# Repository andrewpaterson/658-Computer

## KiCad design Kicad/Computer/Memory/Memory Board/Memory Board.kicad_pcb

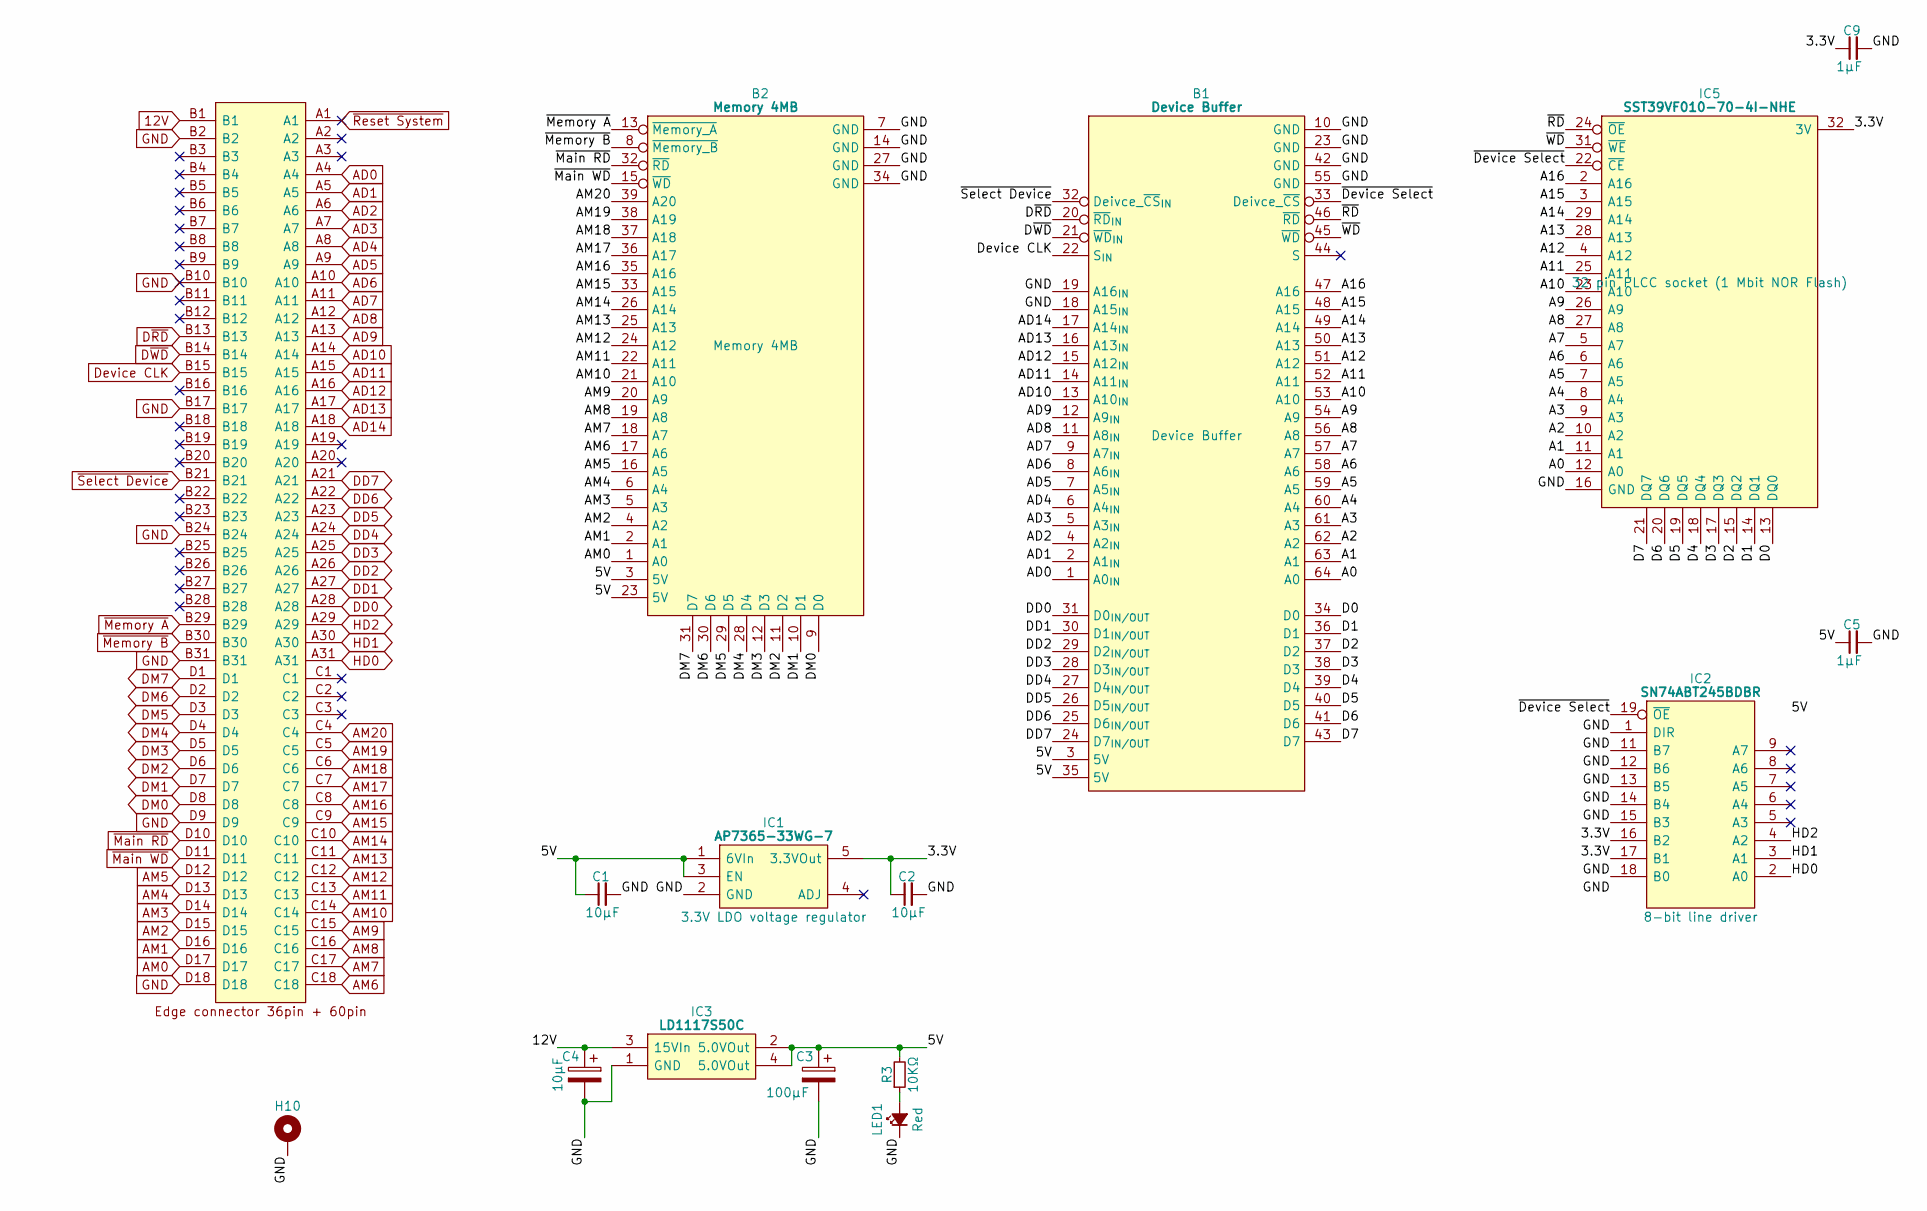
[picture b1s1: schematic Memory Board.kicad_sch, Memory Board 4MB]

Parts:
B1: Device Buffer; HCP65_Device_Buffer
B2: Memory 4MB; HCP65_Memory_4MB
C1, C2: 10µF; C_0805
C3: 100μF; CP_Radial_D4.0mm_P2.00mm
C4: 10μF; CP_Radial_D4.0mm_P2.00mm
C5, C9: 1µF; C_0805
H10: MountingHole_Pad; HCP65_MountingHole_M3_
IC1: AP7365-33WG-7; SOT95P285X130-5N; Manufacturer_Part_Number AP7365-33WG-7; Mouser Part Number 621-AP7365-33WG-7
IC2: SN74ABT245BDBR; SOP65P780X200-20N; Manufacturer_Part_Number SN74ABT245BDBR; Mouser Part Number 595-SN74ABT245BDBR
IC3: LD1117S50C; LD1117S33C; Manufacturer_Part_Number LD1117S50C
IC5: SST39VF010-70-4I-NHE; 5408803224008; Manufacturer_Part_Number SST39VF010-70-4I-NHE
J1: 395-098-520-350; 98pin Edge Connector; Manufacturer_Part_Number 395-098-520-350; Mouser Part Number 587-395-098-520-350
LED1: Red; LED_D5.0mm
R3: 10KΩ; R_0805

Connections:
12V: C4.1, IC3.3 (15VIn), J1.B1
/3.3V: C2.1, C9.1, IC1.5 (3.3VOut), IC2.16 (B2), IC2.17 (B1), IC5.32 (3V)
/5V: B1.3 (5V), B1.35 (5V), B2.3 (5V), B2.23 (5V), C1.1, C3.1, C5.1, IC1.1 (6VIn), IC1.3 (EN), IC2.20 (5V), IC3.2 (5.0VOut), IC3.4 (5.0VOut), R3.2
/A0: B1.64 (A0), IC5.12 (A0)
/A1: B1.63 (A1), IC5.11 (A1)
/A2: B1.62 (A2), IC5.10 (A2)
/A3: B1.61 (A3), IC5.9 (A3)
/A4: B1.60 (A4), IC5.8 (A4)
/A5: B1.59 (A5), IC5.7 (A5)
/A6: B1.58 (A6), IC5.6 (A6)
/A7: B1.57 (A7), IC5.5 (A7)
/A8: B1.56 (A8), IC5.27 (A8)
/A9: B1.54 (A9), IC5.26 (A9)
/A10: B1.53 (A10), IC5.23 (A10)
/A11: B1.52 (A11), IC5.25 (A11)
/A12: B1.51 (A12), IC5.4 (A12)
/A13: B1.50 (A13), IC5.28 (A13)
/A14: B1.49 (A14), IC5.29 (A14)
/A15: B1.48 (A15), IC5.3 (A15)
/A16: B1.47 (A16), IC5.2 (A16)
/D0: B1.34 (D0), IC5.13 (DQ0)
/D1: B1.36 (D1), IC5.14 (DQ1)
/D2: B1.37 (D2), IC5.15 (DQ2)
/D3: B1.38 (D3), IC5.17 (DQ3)
/D4: B1.39 (D4), IC5.18 (DQ4)
/D5: B1.40 (D5), IC5.19 (DQ5)
/D6: B1.41 (D6), IC5.20 (DQ6)
/D7: B1.43 (D7), IC5.21 (DQ7)
/~Device Select: B1.33 (Deivce_~CS), IC2.19 (~OE), IC5.22 (~CE)
/~RD: B1.46 (~RD), IC5.24 (~OE)
/~WD: B1.45 (~WD), IC5.31 (~WE)
AD0: B1.1 (A0_{IN}), J1.A4
AD1: B1.2 (A1_{IN}), J1.A5
AD2: B1.4 (A2_{IN}), J1.A6
AD3: B1.5 (A3_{IN}), J1.A7
AD4: B1.6 (A4_{IN}), J1.A8
AD5: B1.7 (A5_{IN}), J1.A9
AD6: B1.8 (A6_{IN}), J1.A10
AD7: B1.9 (A7_{IN}), J1.A11
AD8: B1.11 (A8_{IN}), J1.A12
AD9: B1.12 (A9_{IN}), J1.A13
AD10: B1.13 (A10_{IN}), J1.A14
AD11: B1.14 (A11_{IN}), J1.A15
AD12: B1.15 (A12_{IN}), J1.A16
AD13: B1.16 (A13_{IN}), J1.A17
AD14: B1.17 (A14_{IN}), J1.A18
AM0: B2.1 (A0), J1.D17
AM1: B2.2 (A1), J1.D16
AM2: B2.4 (A2), J1.D15
AM3: B2.5 (A3), J1.D14
AM4: B2.6 (A4), J1.D13
AM5: B2.16 (A5), J1.D12
AM6: B2.17 (A6), J1.C18
AM7: B2.18 (A7), J1.C17
AM8: B2.19 (A8), J1.C16
AM9: B2.20 (A9), J1.C15
AM10: B2.21 (A10), J1.C14
AM11: B2.22 (A11), J1.C13
AM12: B2.24 (A12), J1.C12
AM13: B2.25 (A13), J1.C11
AM14: B2.26 (A14), J1.C10
AM15: B2.33 (A15), J1.C9
AM16: B2.35 (A16), J1.C8
AM17: B2.36 (A17), J1.C7
AM18: B2.37 (A18), J1.C6
AM19: B2.38 (A19), J1.C5
AM20: B2.39 (A20), J1.C4
AM21: J1.C3
AM22: J1.C2
AM23: J1.C1
DD0: B1.31 (D0_{IN/OUT}), J1.A28
DD1: B1.30 (D1_{IN/OUT}), J1.A27
DD2: B1.29 (D2_{IN/OUT}), J1.A26
DD3: B1.28 (D3_{IN/OUT}), J1.A25
DD4: B1.27 (D4_{IN/OUT}), J1.A24
DD5: B1.26 (D5_{IN/OUT}), J1.A23
DD6: B1.25 (D6_{IN/OUT}), J1.A22
DD7: B1.24 (D7_{IN/OUT}), J1.A21
DM0: B2.9 (D0), J1.D8
DM1: B2.10 (D1), J1.D7
DM2: B2.11 (D2), J1.D6
DM3: B2.12 (D3), J1.D5
DM4: B2.28 (D4), J1.D4
DM5: B2.29 (D5), J1.D3
DM6: B2.30 (D6), J1.D2
DM7: B2.31 (D7), J1.D1
Device CLK: B1.22 (S_{IN}), J1.B15
D~RD: B1.20 (~RD_{IN}), J1.B13
D~WD: B1.21 (~WD_{IN}), J1.B14
GND: B1.10 (GND), B1.18 (A15_{IN}), B1.19 (A16_{IN}), B1.23 (GND), B1.42 (GND), B1.55 (GND), B2.7 (GND), B2.14 (GND), B2.27 (GND), B2.34 (GND), C1.2, C2.2, C3.2, C4.2, C5.2, C9.2, H10.1 (GND), IC1.2 (GND), IC2.1 (DIR), IC2.10 (GND), IC2.11 (B7), IC2.12 (B6), IC2.13 (B5), IC2.14 (B4), IC2.15 (B3), IC2.18 (B0), IC3.1 (GND), IC5.16 (GND), J1.B2, J1.B10, J1.B17, J1.B24, J1.B31, J1.D9, J1.D18, LED1.1 (K)
HD0: IC2.2 (A0), J1.A31
HD1: IC2.3 (A1), J1.A30
HD2: IC2.4 (A2), J1.A29
unnamed: LED1.2 (A), R3.1
~Main RD: B2.32 (~RD), J1.D10
~Main WD: B2.15 (~WD), J1.D11
~Memory A: B2.13 (~Memory_A), J1.B29
~Memory B: B2.8 (~Memory_B), J1.B30
~Reset System: J1.A1
~Select Device: B1.32 (Deivce_~CS_{IN}), J1.B21

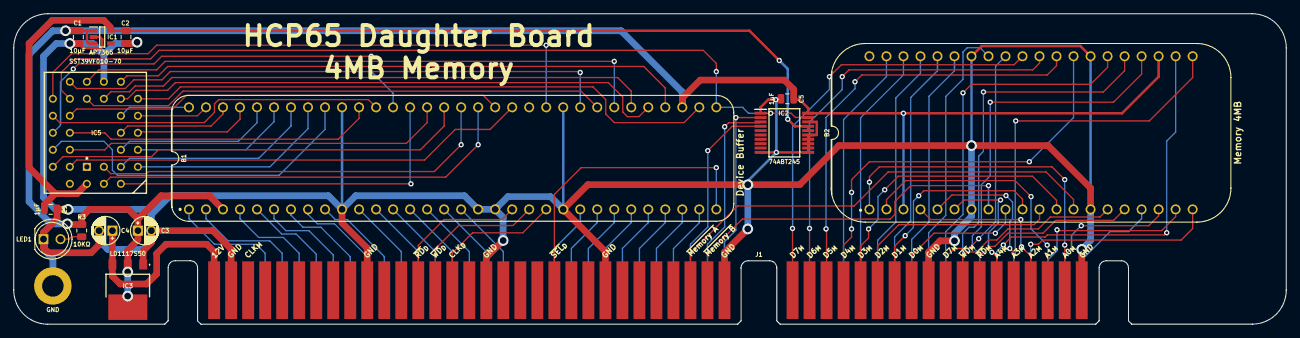
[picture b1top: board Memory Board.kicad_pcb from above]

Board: 2 copper layers, 190.0 x 46.4 mm, 16 parts (0 on the bottom side), 96 nets.

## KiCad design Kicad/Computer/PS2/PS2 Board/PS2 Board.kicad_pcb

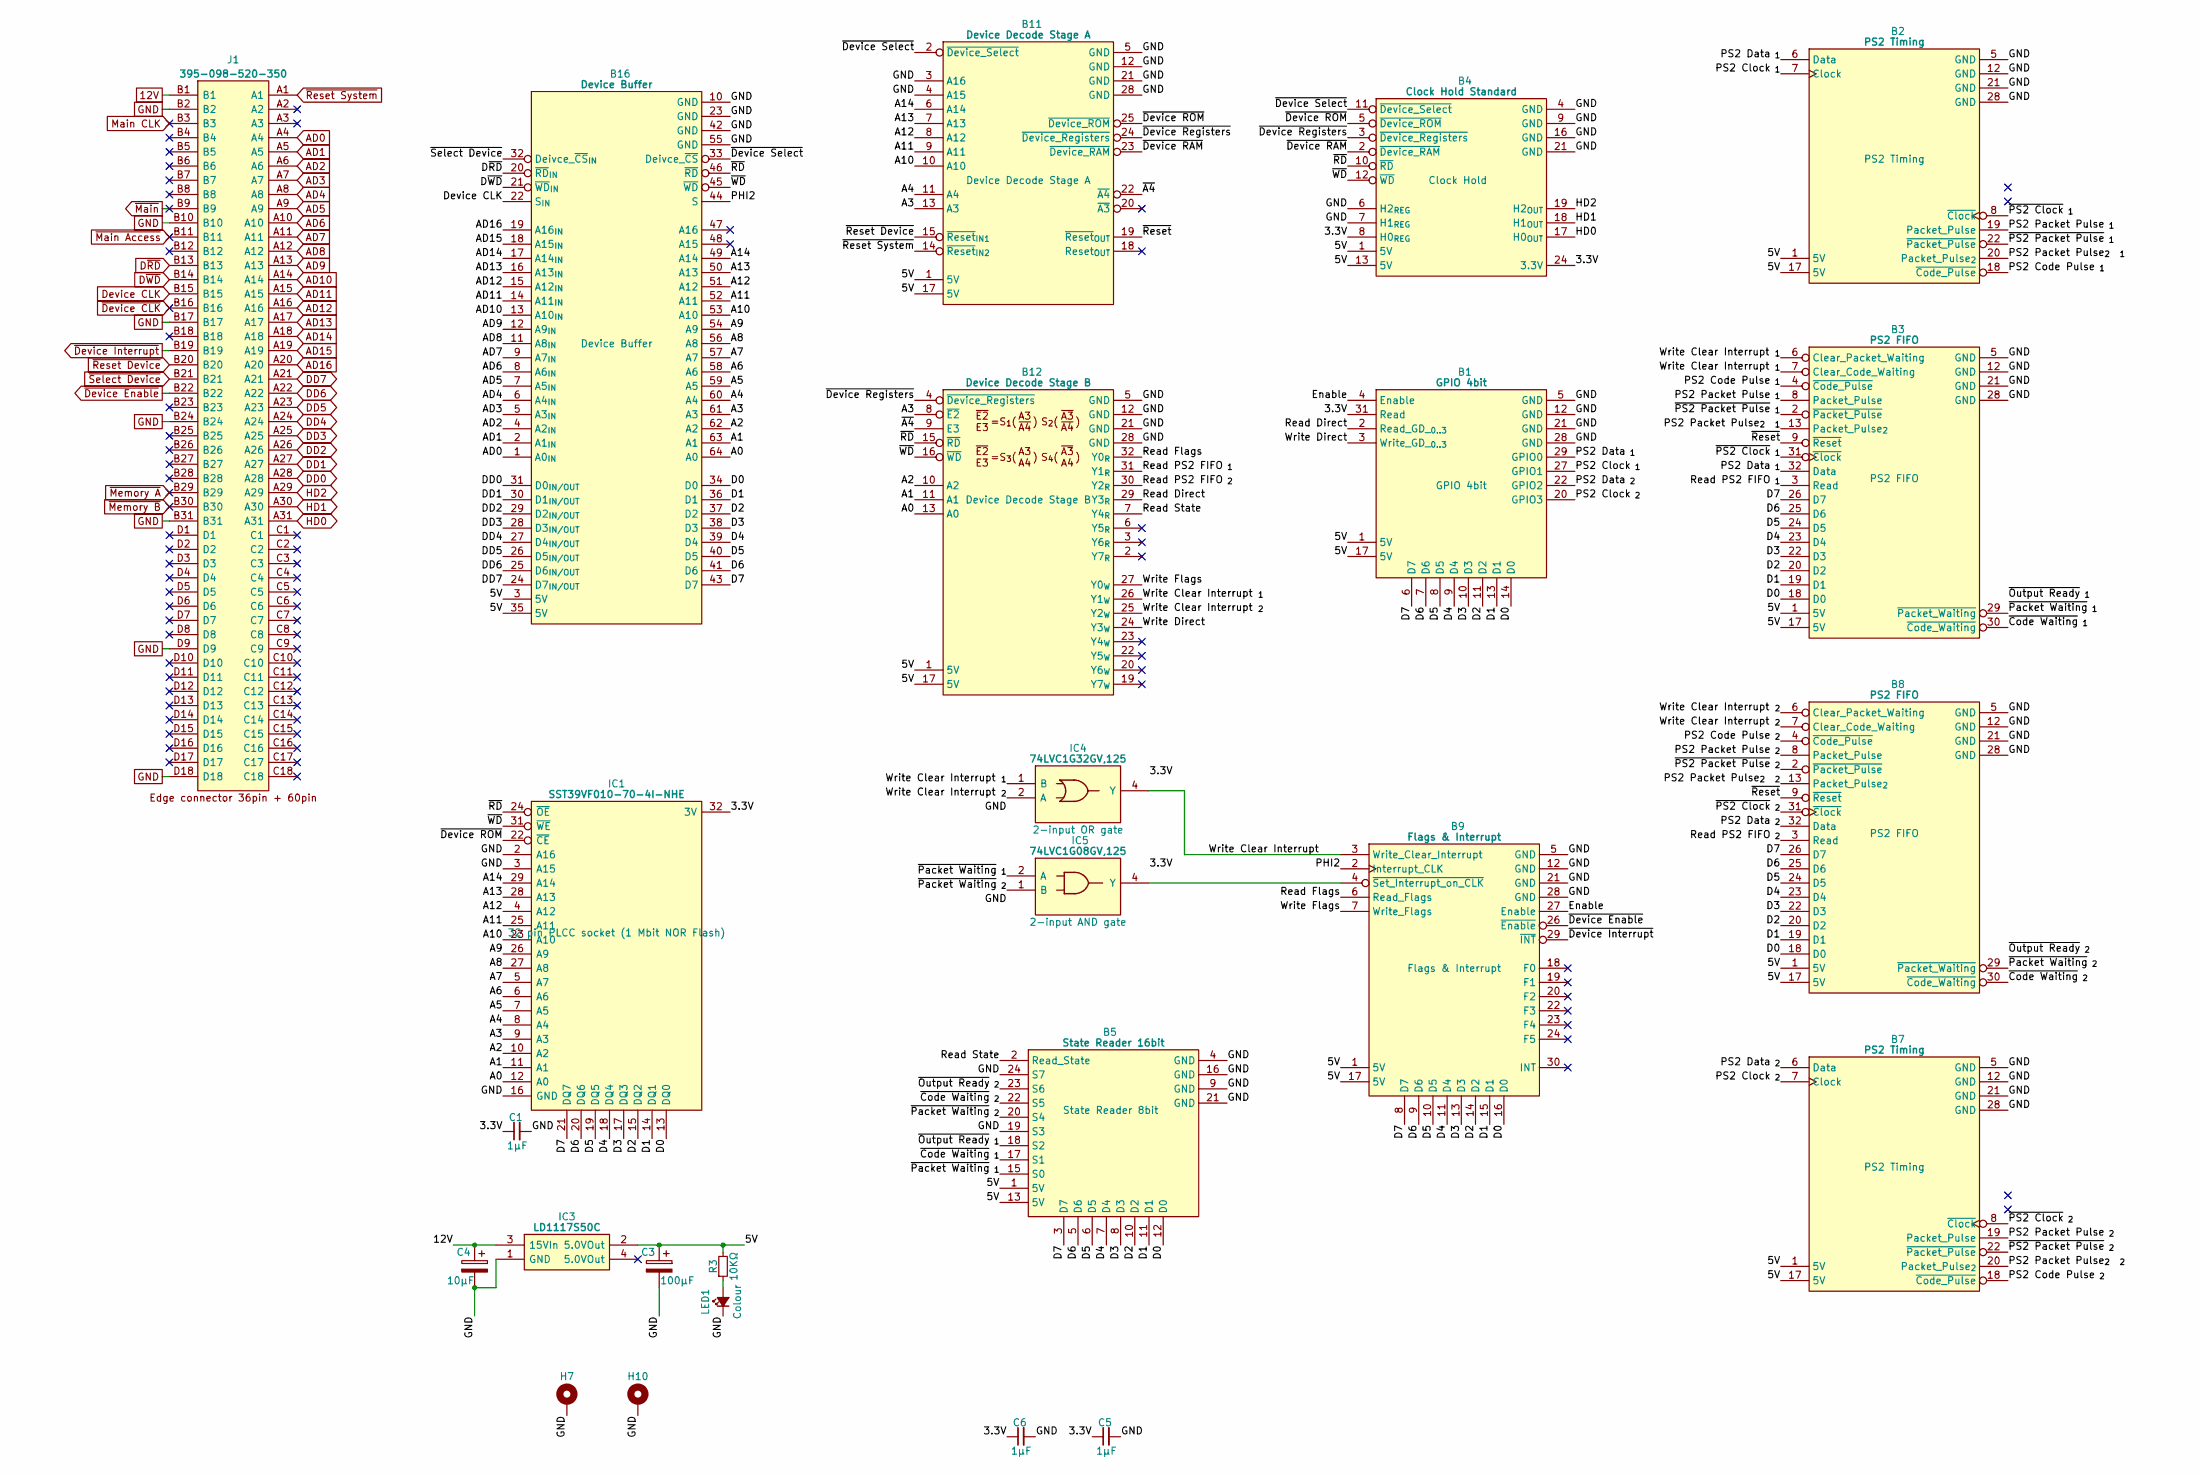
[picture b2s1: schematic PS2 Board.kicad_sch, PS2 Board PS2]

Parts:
B1: GPIO 4bit; HCP65_GPIO_4bit
B2, B7: PS2 Timing; HCP65_PS2_Timing
B3, B8: PS2 FIFO; HCP65_PS2_FIFO
B4: Clock Hold Standard; HCP65_Clock_Hold_Standard
B5: State Reader 16bit; HCP65_State_Reader_8bit
B9: Flags & Interrupt; HCP65_Flags_Interrupt
B11: Device Decode Stage A; HCP65_Device_Decode_Stage_A
B12: Device Decode Stage B; HCP65_Device_Decode_Stage_B
B16: Device Buffer; HCP65_Device_Buffer
C1, C5, C6: 1μF; C_0805
C3: 100μF; CP_Radial_D4.0mm_P2.00mm
C4: 10μF; CP_Radial_D4.0mm_P2.00mm
H7, H10: MountingHole_Pad; HCP65_MountingHole_M3_
IC1: SST39VF010-70-4I-NHE; 5408803224008; Manufacturer_Part_Number SST39VF010-70-4I-NHE
IC3: LD1117S50C; LD1117S33C; Manufacturer_Part_Number LD1117S50C
IC4: 74LVC1G32GV,125; SOT95P275X110-5N; Manufacturer_Part_Number 74LVC1G32GV,125; Mouser Part Number 771-LVC1G32GV125
IC5: 74LVC1G08GV,125; SOT95P275X110-5N; Manufacturer_Part_Number 74LVC1G08GV,125; Mouser Part Number 771-74LVC1G08GV
J1: 395-098-520-350; 98pin Edge Connector; Manufacturer_Part_Number 395-098-520-350; Mouser Part Number 587-395-098-520-350
LED1: Colour; LED_D5.0mm
R3: 10KΩ; R_0805

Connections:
12V: C4.1, IC3.3 (15VIn), J1.B1
/3.3V: B1.31 (Read), B4.8 (H0_{REG}), B4.24 (3.3V), C1.1, C5.1, C6.1, IC1.32 (3V), IC4.5 (3V), IC5.5 (3V)
/5V: B1.1 (5V), B1.17 (5V), B2.1 (5V), B2.17 (5V), B3.1 (5V), B3.17 (5V), B4.1 (5V), B4.13 (5V), B5.1 (5V), B5.13 (5V), B7.1 (5V), B7.17 (5V), B8.1 (5V), B8.17 (5V), B9.1 (5V), B9.17 (5V), B11.1 (5V), B11.17 (5V), B12.1 (5V), B12.17 (5V), B16.3 (5V), B16.35 (5V), C3.1, IC3.2 (5.0VOut), R3.2
/A0: B12.13 (A0), B16.64 (A0), IC1.12 (A0)
/A1: B12.11 (A1), B16.63 (A1), IC1.11 (A1)
/A2: B12.10 (A2), B16.62 (A2), IC1.10 (A2)
/A3: B11.13 (A3), B12.8 (~E2), B16.61 (A3), IC1.9 (A3)
/A4: B11.11 (A4), B16.60 (A4), IC1.8 (A4)
/A5: B16.59 (A5), IC1.7 (A5)
/A6: B16.58 (A6), IC1.6 (A6)
/A7: B16.57 (A7), IC1.5 (A7)
/A8: B16.56 (A8), IC1.27 (A8)
/A9: B16.54 (A9), IC1.26 (A9)
/A10: B11.10 (A10), B16.53 (A10), IC1.23 (A10)
/A11: B11.9 (A11), B16.52 (A11), IC1.25 (A11)
/A12: B11.8 (A12), B16.51 (A12), IC1.4 (A12)
/A13: B11.7 (A13), B16.50 (A13), IC1.28 (A13)
/A14: B11.6 (A14), B16.49 (A14), IC1.29 (A14)
/D0: B1.14 (D0), B3.18 (D0), B5.12 (D0), B8.18 (D0), B9.16 (D0), B16.34 (D0), IC1.13 (DQ0)
/D1: B1.13 (D1), B3.19 (D1), B5.11 (D1), B8.19 (D1), B9.15 (D1), B16.36 (D1), IC1.14 (DQ1)
/D2: B1.11 (D2), B3.20 (D2), B5.10 (D2), B8.20 (D2), B9.14 (D2), B16.37 (D2), IC1.15 (DQ2)
/D3: B1.10 (D3), B3.22 (D3), B5.8 (D3), B8.22 (D3), B9.13 (D3), B16.38 (D3), IC1.17 (DQ3)
/D4: B1.9 (D4), B3.23 (D4), B5.7 (D4), B8.23 (D4), B9.11 (D4), B16.39 (D4), IC1.18 (DQ4)
/D5: B1.8 (D5), B3.24 (D5), B5.6 (D5), B8.24 (D5), B9.10 (D5), B16.40 (D5), IC1.19 (DQ5)
/D6: B1.7 (D6), B3.25 (D6), B5.5 (D6), B8.25 (D6), B9.9 (D6), B16.41 (D6), IC1.20 (DQ6)
/D7: B1.6 (D7), B3.26 (D7), B5.3 (D7), B8.26 (D7), B9.8 (D7), B16.43 (D7), IC1.21 (DQ7)
/Enable: B1.4 (Enable), B9.27 (Enable)
/PHI2: B9.2 (Interrupt_CLK), B16.44 (S)
/PS2 Clock_{ 1}: B1.27 (GPIO1), B2.7 (Clock)
/PS2 Clock_{ 2}: B1.20 (GPIO3), B7.7 (Clock)
/PS2 Code Pulse_{ 1}: B2.18 (~Code_Pulse), B3.4 (~Code_Pulse)
/PS2 Code Pulse_{ 2}: B7.18 (~Code_Pulse), B8.4 (~Code_Pulse)
/PS2 Data_{ 1}: B1.29 (GPIO0), B2.6 (Data), B3.32 (Data)
/PS2 Data_{ 2}: B1.22 (GPIO2), B7.6 (Data), B8.32 (Data)
/PS2 Packet Pulse_{2} _{ 1}: B2.20 (Packet_Pulse_{2}), B3.13 (Packet_Pulse_{2})
/PS2 Packet Pulse_{2} _{ 2}: B7.20 (Packet_Pulse_{2}), B8.13 (Packet_Pulse_{2})
/PS2 Packet Pulse_{ 1}: B2.19 (Packet_Pulse), B3.8 (Packet_Pulse)
/PS2 Packet Pulse_{ 2}: B7.19 (Packet_Pulse), B8.8 (Packet_Pulse)
/Read Direct: B1.2 (Read_GD__{0..3}), B12.29 (Y3_{R})
/Read Flags: B9.6 (Read_Flags), B12.32 (Y0_{R})
/Read PS2 FIFO_{ 1}: B3.3 (Read), B12.31 (Y1_{R})
/Read PS2 FIFO_{ 2}: B8.3 (Read), B12.30 (Y2_{R})
/Read State: B5.2 (Read_State), B12.7 (Y4_{R})
/Write Clear Interrupt: B9.3 (Write_Clear_Interrupt), IC4.4 (Y)
/Write Clear Interrupt _{1}: B3.6 (Clear_Packet_Waiting), B3.7 (Clear_Code_Waiting), B12.26 (Y1_{W}), IC4.1 (B)
/Write Clear Interrupt _{2}: B8.6 (Clear_Packet_Waiting), B8.7 (Clear_Code_Waiting), B12.25 (Y2_{W}), IC4.2 (A)
/Write Direct: B1.3 (Write_GD__{0..3}), B12.24 (Y3_{W})
/Write Flags: B9.7 (Write_Flags), B12.27 (Y0_{W})
/~A4: B11.22 (~A4), B12.9 (E3)
/~Code Waiting_{ 1}: B3.30 (~Code_Waiting), B5.17 (S1)
/~Code Waiting_{ 2}: B5.22 (S5), B8.30 (~Code_Waiting)
/~Device RAM: B4.2 (~Device_RAM), B11.23 (~Device_RAM)
/~Device ROM: B4.5 (~Device_ROM), B11.25 (~Device_ROM), IC1.22 (~CE)
/~Device Registers: B4.3 (~Device_Registers), B11.24 (~Device_Registers), B12.4 (~Device_Registers)
/~Device Select: B4.11 (~Device_Select), B11.2 (~Device_Select), B16.33 (Deivce_~CS)
/~Output Ready_{ 1}: B3.27 (Output_Ready), B5.18 (S2)
/~Output Ready_{ 2}: B5.23 (S6), B8.27 (Output_Ready)
/~PS2 Clock_{ 1}: B2.8 (~Clock), B3.31 (~Clock)
/~PS2 Clock_{ 2}: B7.8 (~Clock), B8.31 (~Clock)
/~PS2 Packet Pulse_{ 1}: B2.22 (~Packet_Pulse), B3.2 (~Packet_Pulse)
/~PS2 Packet Pulse_{ 2}: B7.22 (~Packet_Pulse), B8.2 (~Packet_Pulse)
/~Packet Waiting_{ 1}: B3.29 (~Packet_Waiting), B5.15 (S0), IC5.2 (A)
/~Packet Waiting_{ 2}: B5.20 (S4), B8.29 (~Packet_Waiting), IC5.1 (B)
/~RD: B4.10 (~RD), B12.15 (~RD), B16.46 (~RD), IC1.24 (~OE)
/~Reset: B3.9 (~Reset), B8.9 (~Reset), B11.19 (~Reset_{OUT})
/~WD: B4.12 (~WD), B12.16 (~WD), B16.45 (~WD), IC1.31 (~WE)
AD0: B16.1 (A0_{IN}), J1.A4
AD1: B16.2 (A1_{IN}), J1.A5
AD2: B16.4 (A2_{IN}), J1.A6
AD3: B16.5 (A3_{IN}), J1.A7
AD4: B16.6 (A4_{IN}), J1.A8
AD5: B16.7 (A5_{IN}), J1.A9
AD6: B16.8 (A6_{IN}), J1.A10
AD7: B16.9 (A7_{IN}), J1.A11
AD8: B16.11 (A8_{IN}), J1.A12
AD9: B16.12 (A9_{IN}), J1.A13
AD10: B16.13 (A10_{IN}), J1.A14
AD11: B16.14 (A11_{IN}), J1.A15
AD12: B16.15 (A12_{IN}), J1.A16
AD13: B16.16 (A13_{IN}), J1.A17
AD14: B16.17 (A14_{IN}), J1.A18
AD15: B16.18 (A15_{IN}), J1.A19
AD16: B16.19 (A16_{IN}), J1.A20
DD0: B16.31 (D0_{IN/OUT}), J1.A28
DD1: B16.30 (D1_{IN/OUT}), J1.A27
DD2: B16.29 (D2_{IN/OUT}), J1.A26
DD3: B16.28 (D3_{IN/OUT}), J1.A25
DD4: B16.27 (D4_{IN/OUT}), J1.A24
DD5: B16.26 (D5_{IN/OUT}), J1.A23
DD6: B16.25 (D6_{IN/OUT}), J1.A22
DD7: B16.24 (D7_{IN/OUT}), J1.A21
Device CLK: B16.22 (S_{IN}), J1.B15
D~RD: B16.20 (~RD_{IN}), J1.B13
D~WD: B16.21 (~WD_{IN}), J1.B14
GND: B1.5 (GND), B1.12 (GND), B1.21 (GND), B1.28 (GND), B2.5 (GND), B2.12 (GND), B2.21 (GND), B2.28 (GND), B3.5 (GND), B3.12 (GND), B3.21 (GND), B3.28 (GND), B4.4 (GND), B4.6 (H2_{REG}), B4.7 (H1_{REG}), B4.9 (GND), B4.16 (GND), B4.21 (GND), B5.4 (GND), B5.9 (GND), B5.16 (GND), B5.19 (S3), B5.21 (GND), B5.24 (S7), B7.5 (GND), B7.12 (GND), B7.21 (GND), B7.28 (GND), B8.5 (GND), B8.12 (GND), B8.21 (GND), B8.28 (GND), B9.5 (GND), B9.12 (GND), B9.21 (GND), B9.28 (GND), B11.3 (A16), B11.4 (A15), B11.5 (GND), B11.12 (GND), B11.21 (GND), B11.28 (GND), B12.5 (GND), B12.12 (GND), B12.21 (GND), B12.28 (GND), B16.10 (GND), B16.23 (GND), B16.42 (GND), B16.55 (GND), C1.2, C3.2, C4.2, C5.2, C6.2, H7.1 (GND), H10.1 (GND), IC1.2 (A16), IC1.3 (A15), IC1.16 (GND), IC3.1 (GND), IC4.3 (GND), IC5.3 (GND), J1.B2, J1.B10, J1.B17, J1.B24, J1.B31, J1.D9, J1.D18, LED1.1 (K)
HD0: B4.17 (H0_{OUT}), J1.A31
HD1: B4.18 (H1_{OUT}), J1.A30
HD2: B4.19 (H2_{OUT}), J1.A29
Main CLK: J1.B3
unnamed: B9.4 (~Set_Interrupt_on_CLK), IC5.4 (Y)
unnamed: LED1.2 (A), R3.1
~Device CLK: J1.B16
~Device Enable: B9.26 (~Enable), J1.B22
~Device Interrupt: B9.29 (~INT), J1.B19
~Main Access: J1.B11
~Main: J1.B9
~Memory A: J1.B29
~Memory B: J1.B30
~Reset Device: B11.15 (~Reset_{IN1}), J1.B20
~Reset System: B11.14 (~Reset_{IN2}), J1.A1
~Select Device: B16.32 (Deivce_~CS_{IN}), J1.B21

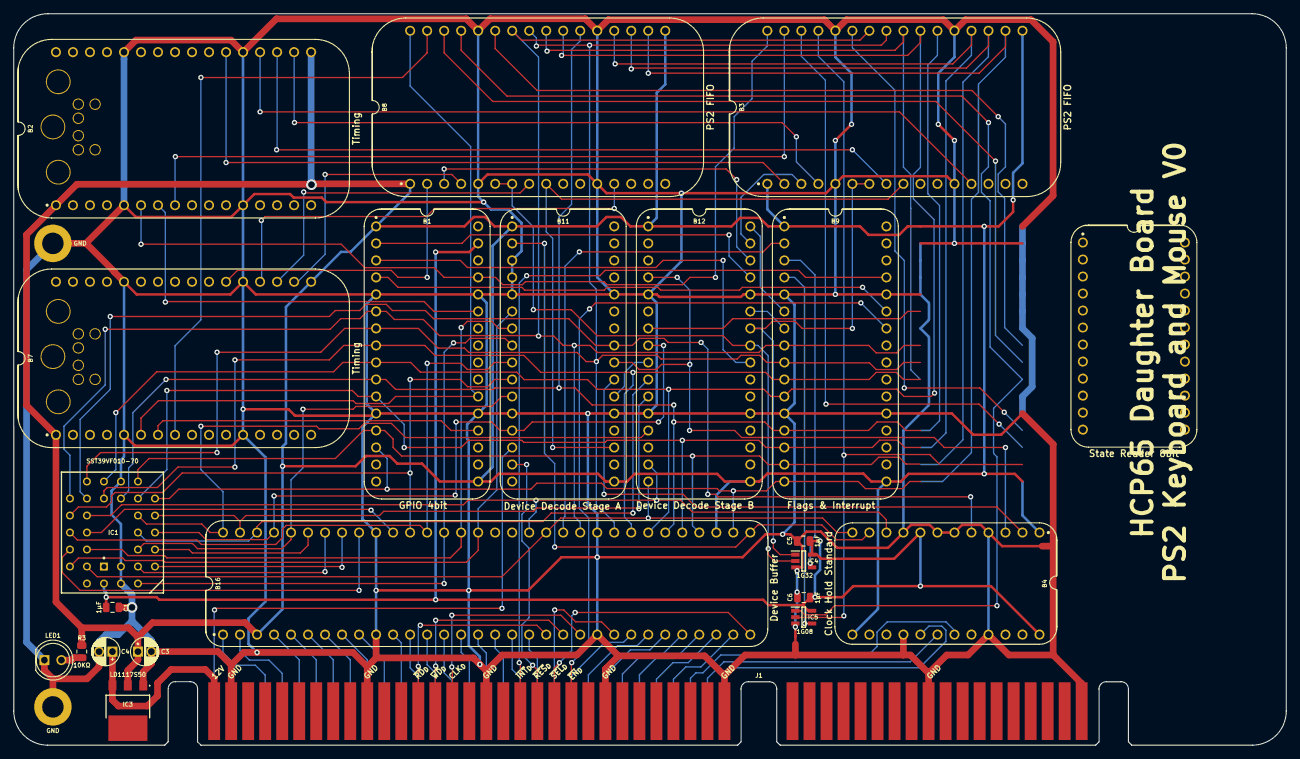
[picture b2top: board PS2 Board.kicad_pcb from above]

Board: 2 copper layers, 190.0 x 109.2 mm, 25 parts (0 on the bottom side), 105 nets.

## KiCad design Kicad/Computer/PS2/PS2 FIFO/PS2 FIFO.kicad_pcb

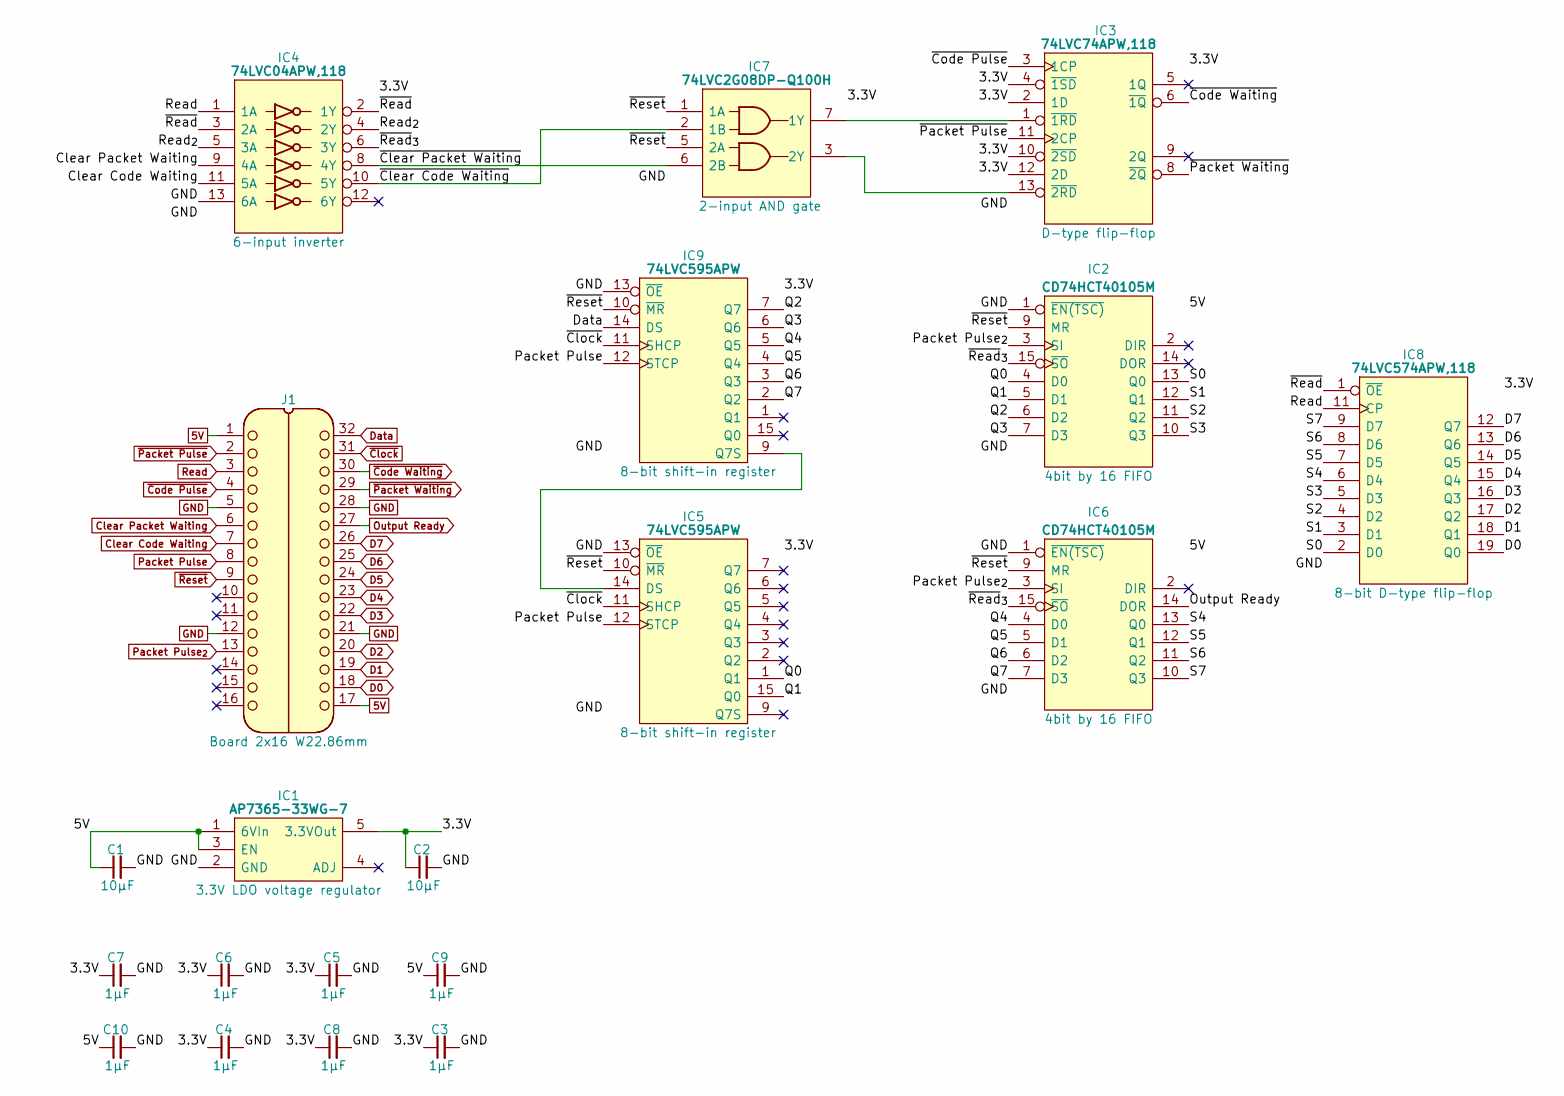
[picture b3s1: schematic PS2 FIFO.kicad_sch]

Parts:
C1, C2: 10μF; C_0805
C3, C4, C5, C6, C7, C8, C9, C10: 1μF; C_0805
IC1: AP7365-33WG-7; SOT95P285X130-5N; Manufacturer_Part_Number AP7365-33WG-7; Mouser Part Number 621-AP7365-33WG-7
IC2, IC6: CD74HCT40105M; SOIC127P600X175-16N; Manufacturer_Part_Number CD74HCT40105M
IC3: 74LVC74APW,118; SOP65P640X110-14N; Mouser Part Number 771-74LVC74APW-T
IC4: 74LVC04APW,118; SOP65P640X110-14N; Manufacturer_Part_Number 74LVC04APW,118; Mouser Part Number 771-74LVC04APW-T
IC5, IC9: 74LVC595APW; SOP65P640X110-16N; Mouser Part Number 771-74LVC595AD
IC7: 74LVC2G08DP-Q100H; SOP65P400X110-8N; Manufacturer_Part_Number 74LVC2G08DP-Q100H; Mouser Part Number 771-74LVC2G08DPQ100H
IC8: 74LVC574APW,118; SOP65P640X110-20N; Manufacturer_Part_Number 74LVC574APW,118; Mouser Part Number 771-74LVC574APW-T
J1: Board 2x16 W22.86mm; DIP-32_Board_W22.86mm

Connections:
5V: C1.1, C9.1, C10.1, IC1.1 (6VIn), IC1.3 (EN), IC2.16 (5V), IC6.16 (5V), J1.1, J1.17
/3.3V: C2.1, C3.1, C4.1, C5.1, C6.1, C7.1, C8.1, IC1.5 (3.3VOut), IC3.2 (1D), IC3.4 (~1SD), IC3.10 (~2SD), IC3.12 (2D), IC3.14 (3V), IC4.14 (3V), IC5.16 (3V), IC7.8 (3V), IC8.20 (3V), IC9.16 (3V)
/Q0: IC2.4 (D0), IC5.1 (Q1)
/Q1: IC2.5 (D1), IC5.15 (Q0)
/Q2: IC2.6 (D2), IC9.7 (Q7)
/Q3: IC2.7 (D3), IC9.6 (Q6)
/Q4: IC6.4 (D0), IC9.5 (Q5)
/Q5: IC6.5 (D1), IC9.4 (Q4)
/Q6: IC6.6 (D2), IC9.3 (Q3)
/Q7: IC6.7 (D3), IC9.2 (Q2)
/Read_{2}: IC4.4 (2Y), IC4.5 (3A)
/S0: IC2.13 (Q0), IC8.2 (D0)
/S1: IC2.12 (Q1), IC8.3 (D1)
/S2: IC2.11 (Q2), IC8.4 (D2)
/S3: IC2.10 (Q3), IC8.5 (D3)
/S4: IC6.13 (Q0), IC8.6 (D4)
/S5: IC6.12 (Q1), IC8.7 (D5)
/S6: IC6.11 (Q2), IC8.8 (D6)
/S7: IC6.10 (Q3), IC8.9 (D7)
/~Clear Code Waiting: IC4.10 (5Y), IC7.2 (1B)
/~Clear Packet Waiting: IC4.8 (4Y), IC7.6 (2B)
/~Read: IC4.2 (1Y), IC4.3 (2A), IC8.1 (~OE)
/~Read_{3}: IC2.15 (~SO), IC4.6 (3Y), IC6.15 (~SO)
Clear Code Waiting: IC4.11 (5A), J1.7
Clear Packet Waiting: IC4.9 (4A), J1.6
D0: IC8.19 (Q0), J1.18
D1: IC8.18 (Q1), J1.19
D2: IC8.17 (Q2), J1.20
D3: IC8.16 (Q3), J1.22
D4: IC8.15 (Q4), J1.23
D5: IC8.14 (Q5), J1.24
D6: IC8.13 (Q6), J1.25
D7: IC8.12 (Q7), J1.26
Data: IC9.14 (DS), J1.32
GND: C1.2, C2.2, C3.2, C4.2, C5.2, C6.2, C7.2, C8.2, C9.2, C10.2, IC1.2 (GND), IC2.1 (~EN(TSC)), IC2.8 (GND), IC3.7 (GND), IC4.7 (GND), IC4.13 (6A), IC5.8 (GND), IC5.13 (~OE), IC6.1 (~EN(TSC)), IC6.8 (GND), IC7.4 (GND), IC8.10 (GND), IC9.8 (GND), IC9.13 (~OE), J1.5, J1.12, J1.21, J1.28
unnamed: IC3.1 (~1RD), IC7.7 (1Y)
unnamed: IC3.13 (~2RD), IC7.3 (2Y)
unnamed: IC5.14 (DS), IC9.9 (Q7S)
Output Ready: IC6.14 (DOR), J1.27
Packet Pulse: IC5.12 (STCP), IC9.12 (STCP), J1.8
Packet Pulse_{2}: IC2.3 (SI), IC6.3 (SI), J1.13
Read: IC4.1 (1A), IC8.11 (CP), J1.3
~Clock: IC5.11 (SHCP), IC9.11 (SHCP), J1.31
~Code Pulse: IC3.3 (1CP), J1.4
~Code Waiting: IC3.6 (~1Q), J1.30
~Packet Pulse: IC3.11 (2CP), J1.2
~Packet Waiting: IC3.8 (~2Q), J1.29
~Reset: IC2.9 (MR), IC5.10 (~MR), IC6.9 (MR), IC7.1 (1A), IC7.5 (2A), IC9.10 (~MR), J1.9

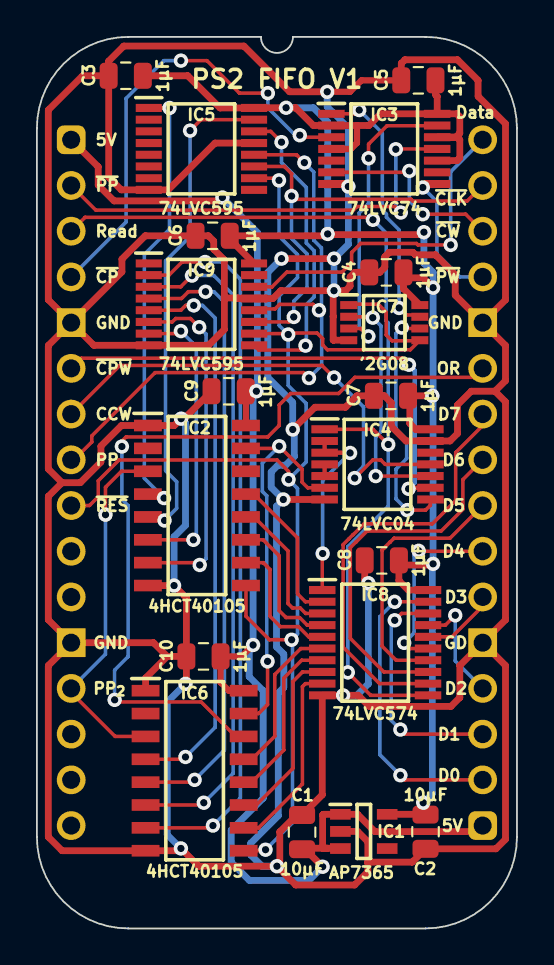
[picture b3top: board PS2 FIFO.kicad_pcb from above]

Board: 2 copper layers, 26.7 x 49.5 mm, 20 parts (0 on the bottom side), 48 nets.

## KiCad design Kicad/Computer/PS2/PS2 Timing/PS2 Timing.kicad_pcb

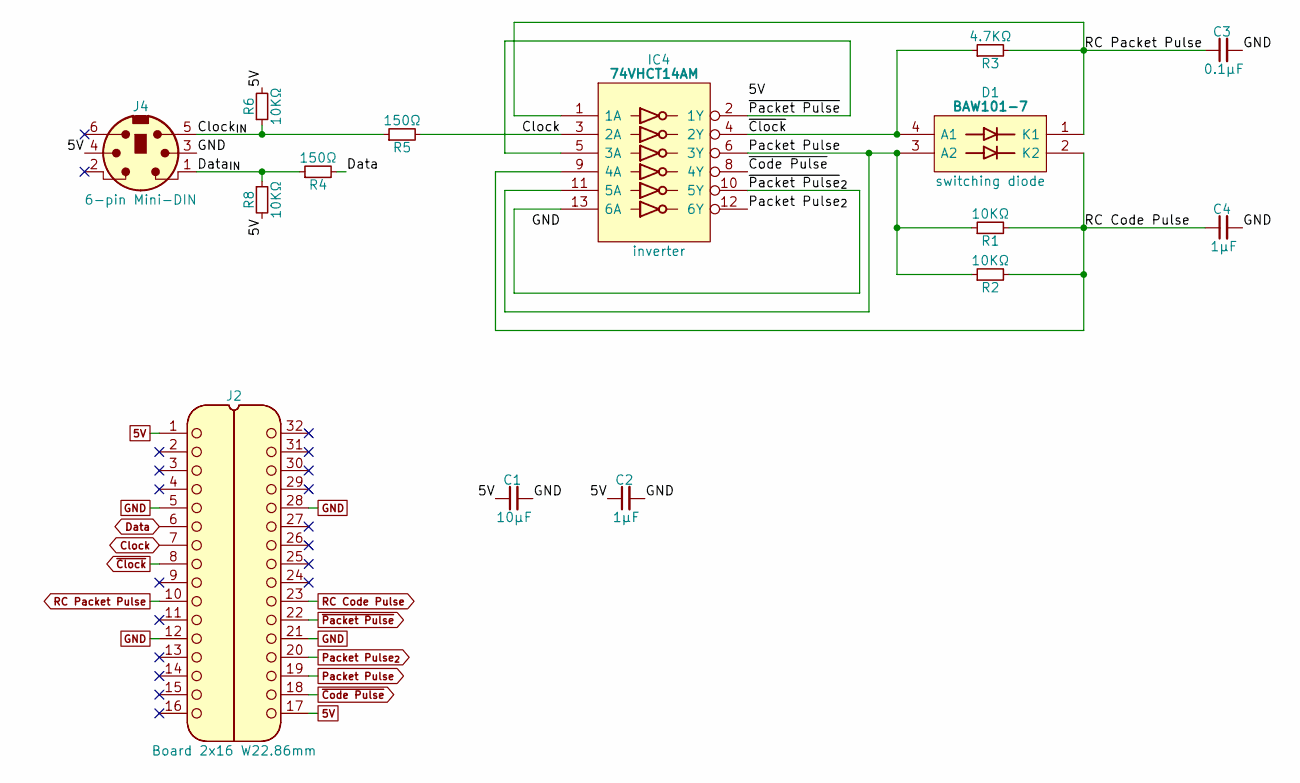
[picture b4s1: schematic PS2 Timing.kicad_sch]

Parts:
C1: 10μF; C_0805
C2, C4: 1μF; C_0805
C3: 0.1μF; C_0805
D1: BAW101-7; BAW1017; Manufacturer_Part_Number BAW101-7; Mouser Part Number 621-BAW101-7
IC4: 74VHCT14AM; SOIC127P600X175-14N; Manufacturer_Part_Number 74VHCT14AM; Mouser Part Number 512-74VHCT14AM
J2: Board 2x16 W22.86mm; DIP-32_Board_W22.86mm
J4: TM-0508 A/6; TM0508A6
R1, R2, R6, R8: 10KΩ; R_0805
R3: 4.7KΩ; R_0805
R4, R5: 150Ω; R_0805

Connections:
5V: C1.1, C2.1, IC4.14 (5V), J2.1, J2.17, J4.4, R6.2, R8.2
/Clock_{IN}: J4.5, R5.1, R6.1
/Data_{IN}: J4.1, R4.1, R8.1
/~Packet Pulse_{2}: IC4.10 (5Y), IC4.13 (6A)
Clock: IC4.3 (2A), J2.7, R5.2
Data: J2.6, R4.2
GND: C1.2, C2.2, C3.2, C4.2, IC4.7 (GND), J2.5, J2.12, J2.21, J2.28, J4.3
Packet Pulse: D1.3 (A2), IC4.6 (3Y), IC4.11 (5A), J2.19, R1.1, R2.1
Packet Pulse_{2}: IC4.12 (6Y), J2.20
RC Code Pulse: C4.1, D1.2 (K2), IC4.9 (4A), J2.23, R1.2, R2.2
RC Packet Pulse: C3.1, D1.1 (K1), IC4.1 (1A), J2.10, R3.2
~Clock: D1.4 (A1), IC4.4 (2Y), J2.8, R3.1
~Code Pulse: IC4.8 (4Y), J2.18
~Packet Pulse: IC4.2 (1Y), IC4.5 (3A), J2.22

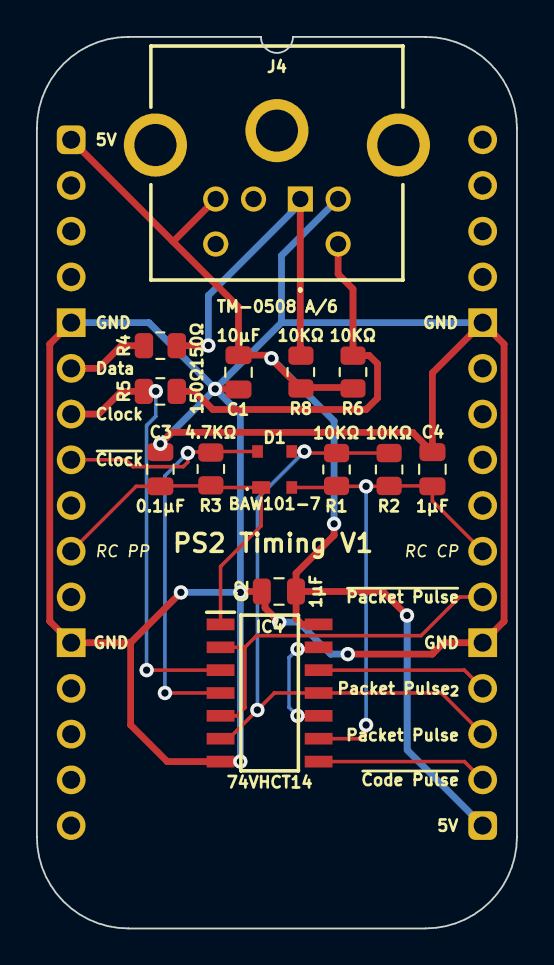
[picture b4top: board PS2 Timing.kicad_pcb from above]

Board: 2 copper layers, 26.7 x 49.5 mm, 15 parts (0 on the bottom side), 14 nets.
